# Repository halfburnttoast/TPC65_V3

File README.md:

# TPC65_V3
65C816 computer madness

This build replaces the TPC65-V2's CPU with a 65C816. It offers massive improvements, but requires additional circuitry to use bank switching.
On first boot, the CPU defaults to emulation mode. In emulation mode, the computer should be completely backwards compatible with V2 of this computer and all sofware. 

When emulation mode is turned off (see 65C816 datasheet for opcode sequence), the computer switches to 16-bit mode with a 24-bit (banked) address bus. 

Unfortunately, because of emulation mode, EEPROM must be located at the top-end of page 1 (0x000000 - 0x00FFFF). Because it follows the same memory map as V2, the memory map looks like this:

0x000000-0x007FFF - Base SRAM

0x008000-0x00BFFF - Memory-mapped IO

0x00C000-0x00FFFF - Base EEPROM + system vectors

Anything at or above 0x010000 is extended memory and requires banking through the 74x573 and 74x245. https://www.westerndesigncenter.com/wdc/documentation/w65c816s.pdf (page-44). 

The extended memory is currently mapped to the remaining address pins of the SRAM, which should give about 450K of extended RAM. Expanding EEPROM is not a priority as this computer has a built-in SD card module slot and is inteded to use the SD card for larger program loading.

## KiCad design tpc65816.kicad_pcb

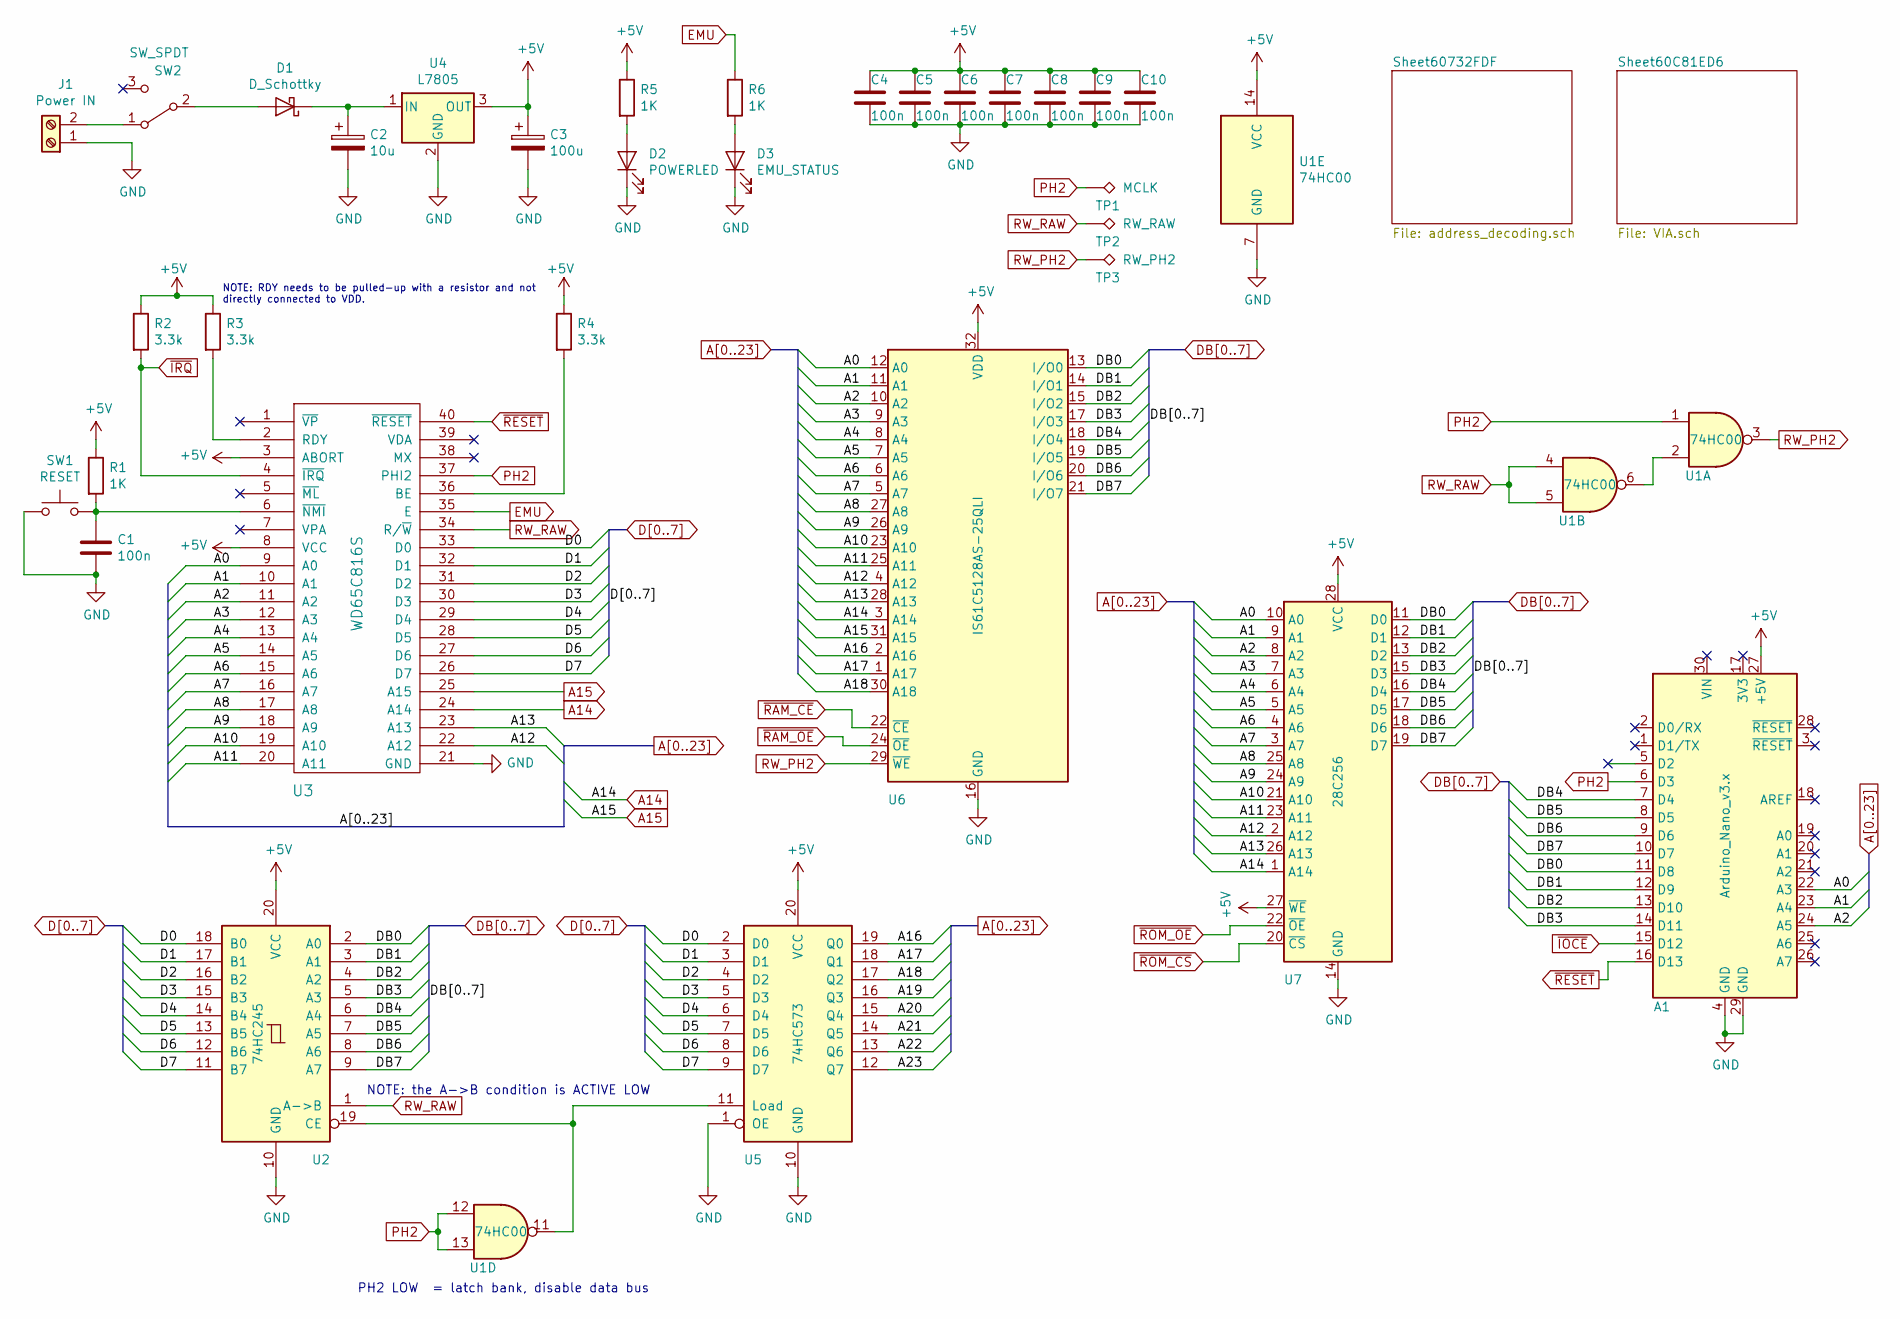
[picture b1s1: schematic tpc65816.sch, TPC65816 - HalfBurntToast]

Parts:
A1: Arduino_Nano_v3.x; Arduino_Nano
C1, C4, C5, C6, C7, C8, C9, C10: 100n; C_1206_3216Metric_Pad1.42x1.75mm_HandSolder
C2: 10u; CP_Radial_D4.0mm_P2.00mm
C3: 100u; CP_Radial_D4.0mm_P2.00mm
D1: D_Schottky; D_1206_3216Metric_Pad1.42x1.75mm_HandSolder
D2: POWERLED; LED_D5.0mm
D3: EMU_STATUS; LED_1206_3216Metric_Pad1.42x1.75mm_HandSolder
J1: Power IN; TerminalBlock_bornier-2_P5.08mm
R1, R5, R6: 1K; R_1206_3216Metric_Pad1.42x1.75mm_HandSolder
R2: 3.3k; R_Axial_DIN0207_L6.3mm_D2.5mm_P7.62mm_Horizontal
R3, R4: 3.3k; R_1206_3216Metric_Pad1.42x1.75mm_HandSolder
SW1: RESET; SW_PUSH_6mm
SW2: SW_SPDT; spdt_slide_switch
TP1: MCLK; TestPoint_Pad_1.0x1.0mm
TP2: RW_RAW; TestPoint_Pad_1.0x1.0mm
TP3: RW_PH2; TestPoint_Pad_1.0x1.0mm
U1: 74HC00; SOIC-14_3.9x8.7mm_P1.27mm
U2: 74HC245; SOIC-20W_7.5x12.8mm_P1.27mm
U3: WD65C816S; DIP-40_W15.24mm_Socket
U4: L7805; TO-220F-3_Horizontal_TabDown
U5: 74HC573; SOIC-20W_7.5x12.8mm_P1.27mm
U6: IS61C5128AS-25QLI; SSOP-32_11.305x20.495mm_P1.27mm
U7: 28C256; DIP-28_W15.24mm_Socket

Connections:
+5V: A1.27 (+5V), C3.1, C4.1, C5.1, C6.1, C7.1, C8.1, C9.1, C10.1, R1.1, R2.1, R3.1, R4.1, R5.1, U1.14 (VCC), U2.20 (VCC), U3.3 (ABORT), U3.8 (VCC), U4.3 (OUT), U5.20 (VCC), U6.32 (VDD), U7.27 (~WE), U7.28 (VCC); also elsewhere on the board
A0: A1.22 (A3), U3.9 (A0), U6.12 (A0), U7.10 (A0)
A1: A1.23 (A4), U3.10 (A1), U6.11 (A1), U7.9 (A1)
A2: A1.24 (A5), U3.11 (A2), U6.10 (A2), U7.8 (A2)
A3: U3.12 (A3), U6.9 (A3), U7.7 (A3); also elsewhere on the board
A4: U3.13 (A4), U6.8 (A4), U7.6 (A4); also elsewhere on the board
A5: U3.14 (A5), U6.7 (A5), U7.5 (A5); also elsewhere on the board
A6: U3.15 (A6), U6.6 (A6), U7.4 (A6); also elsewhere on the board
A7: U3.16 (A7), U6.5 (A7), U7.3 (A7); also elsewhere on the board
A8: U3.17 (A8), U6.27 (A8), U7.25 (A8); also elsewhere on the board
A9: U3.18 (A9), U6.26 (A9), U7.24 (A9)
A10: U3.19 (A10), U6.23 (A10), U7.21 (A10)
A11: U3.20 (A11), U6.25 (A11), U7.23 (A11)
A12: U3.22 (A12), U6.4 (A12), U7.2 (A12)
A13: U3.23 (A13), U6.28 (A13), U7.26 (A13)
A14: U3.24 (A14), U6.3 (A14), U7.1 (A14); also elsewhere on the board
A15: U3.25 (A15), U6.31 (A15); also elsewhere on the board
A16: U5.19 (Q0), U6.2 (A16); also elsewhere on the board
A17: U5.18 (Q1), U6.1 (A17); also elsewhere on the board
A18: U5.17 (Q2), U6.30 (A18); also elsewhere on the board
A19: U5.16 (Q3); also elsewhere on the board
A20: U5.15 (Q4); also elsewhere on the board
A21: U5.14 (Q5); also elsewhere on the board
A22: U5.13 (Q6); also elsewhere on the board
A23: U5.12 (Q7); also elsewhere on the board
D0: U2.18 (B0), U3.33 (D0), U5.2 (D0)
D1: U2.17 (B1), U3.32 (D1), U5.3 (D1)
D2: U2.16 (B2), U3.31 (D2), U5.4 (D2)
D3: U2.15 (B3), U3.30 (D3), U5.5 (D3)
D4: U2.14 (B4), U3.29 (D4), U5.6 (D4)
D5: U2.13 (B5), U3.28 (D5), U5.7 (D5)
D6: U2.12 (B6), U3.27 (D6), U5.8 (D6)
D7: U2.11 (B7), U3.26 (D7), U5.9 (D7)
DB0: A1.11 (D8), U2.2 (A0), U6.13 (I/O0), U7.11 (D0); also elsewhere on the board
DB1: A1.12 (D9), U2.3 (A1), U6.14 (I/O1), U7.12 (D1); also elsewhere on the board
DB2: A1.13 (D10), U2.4 (A2), U6.15 (I/O2), U7.13 (D2); also elsewhere on the board
DB3: A1.14 (D11), U2.5 (A3), U6.17 (I/O3), U7.15 (D3); also elsewhere on the board
DB4: A1.7 (D4), U2.6 (A4), U6.18 (I/O4), U7.16 (D4); also elsewhere on the board
DB5: A1.8 (D5), U2.7 (A5), U6.19 (I/O5), U7.17 (D5); also elsewhere on the board
DB6: A1.9 (D6), U2.8 (A6), U6.20 (I/O6), U7.18 (D6); also elsewhere on the board
DB7: A1.10 (D7), U2.9 (A7), U6.21 (I/O7), U7.19 (D7); also elsewhere on the board
EMU: R6.1, U3.35 (E)
GND: A1.4 (GND), A1.29 (GND), C1.2, C2.2, C3.2, C4.2, C5.2, C6.2, C7.2, C8.2, C9.2, C10.2, D2.1 (K), D3.1 (K), J1.1, SW1.1, U1.7 (GND), U2.10 (GND), U3.21 (GND), U4.2 (GND), U5.1 (OE), U5.10 (GND), U6.16 (GND), U7.14 (GND); also elsewhere on the board
unnamed: C1.1, R1.2, SW1.2, U3.6 (~NMI)
unnamed: C2.1, D1.1 (K), U4.1 (IN)
unnamed: D1.2 (A), SW2.2 (B)
unnamed: D2.2 (A), R5.2
unnamed: D3.2 (A), R6.2
unnamed: J1.2, SW2.1 (A)
unnamed: R3.2, U3.2 (RDY)
unnamed: R4.2, U3.36 (BE)
unnamed: U1.2, U1.6
unnamed: U1.11, U2.19 (CE), U5.11 (Load)
PH2: A1.6 (D3), TP1.1, U1.1, U1.12, U1.13, U3.37 (PHI2); also elsewhere on the board
RW_PH2: TP3.1, U1.3, U6.29 (~WE)
RW_RAW: TP2.1, U1.4, U1.5, U2.1 (A->B), U3.34 (R/~W); also elsewhere on the board
~IOCE: A1.15 (D12); also elsewhere on the board
~IRQ: R2.2, U3.4 (~IRQ); also elsewhere on the board
~RAM_CE: U6.22 (~CE), U6.24 (~OE); also elsewhere on the board
~RESET: A1.16 (D13), U3.40 (~RESET); also elsewhere on the board
~ROM_CS: U7.20 (~CS), U7.22 (~OE); also elsewhere on the board

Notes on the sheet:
NOTE: RDY needs to be pulled-up with a resistor and not directly connected to VDD.
NOTE: the A->B condition is ACTIVE LOW
PH2 LOW = latch bank, disable data bus

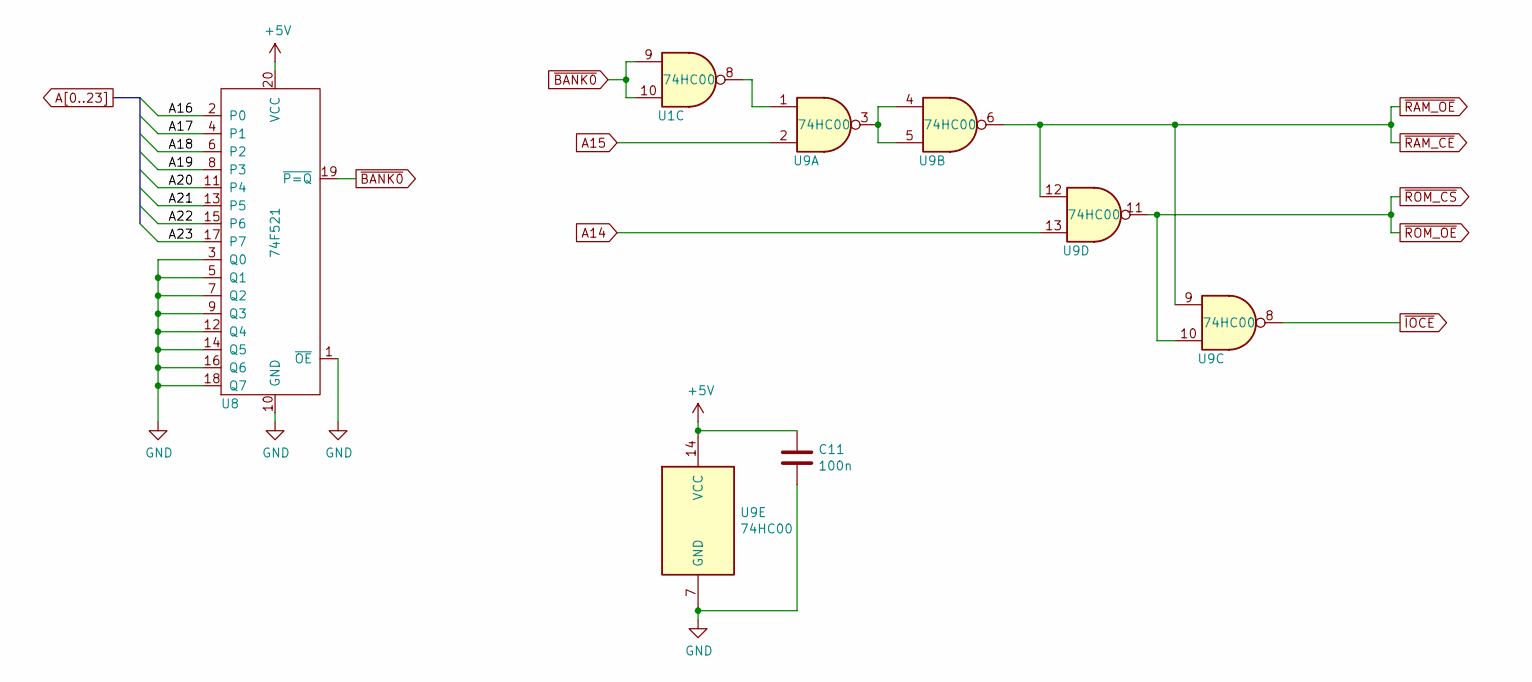
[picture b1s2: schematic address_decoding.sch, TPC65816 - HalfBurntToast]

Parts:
C11: 100n; C_1206_3216Metric_Pad1.42x1.75mm_HandSolder
U1, U9: 74HC00; SOIC-14_3.9x8.7mm_P1.27mm
U8: 74F521; SOIC-20W_7.5x12.8mm_P1.27mm

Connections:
+5V: C11.1, U8.20 (VCC), U9.14 (VCC); also elsewhere on the board
A14: U9.13; also elsewhere on the board
A15: U9.2; also elsewhere on the board
A16: U8.2 (P0); also elsewhere on the board
A17: U8.4 (P1); also elsewhere on the board
A18: U8.6 (P2); also elsewhere on the board
A19: U8.8 (P3); also elsewhere on the board
A20: U8.11 (P4); also elsewhere on the board
A21: U8.13 (P5); also elsewhere on the board
A22: U8.15 (P6); also elsewhere on the board
A23: U8.17 (P7); also elsewhere on the board
GND: C11.2, U8.1 (~OE), U8.3 (Q0), U8.5 (Q1), U8.7 (Q2), U8.9 (Q3), U8.10 (GND), U8.12 (Q4), U8.14 (Q5), U8.16 (Q6), U8.18 (Q7), U9.7 (GND); also elsewhere on the board
unnamed: U1.8, U9.1
unnamed: U9.3, U9.4, U9.5
~BANK0: U1.9, U1.10, U8.19 (~P=Q)
~IOCE: U9.8; also elsewhere on the board
~RAM_CE: U9.6, U9.9, U9.12; also elsewhere on the board
~ROM_CS: U9.10, U9.11; also elsewhere on the board

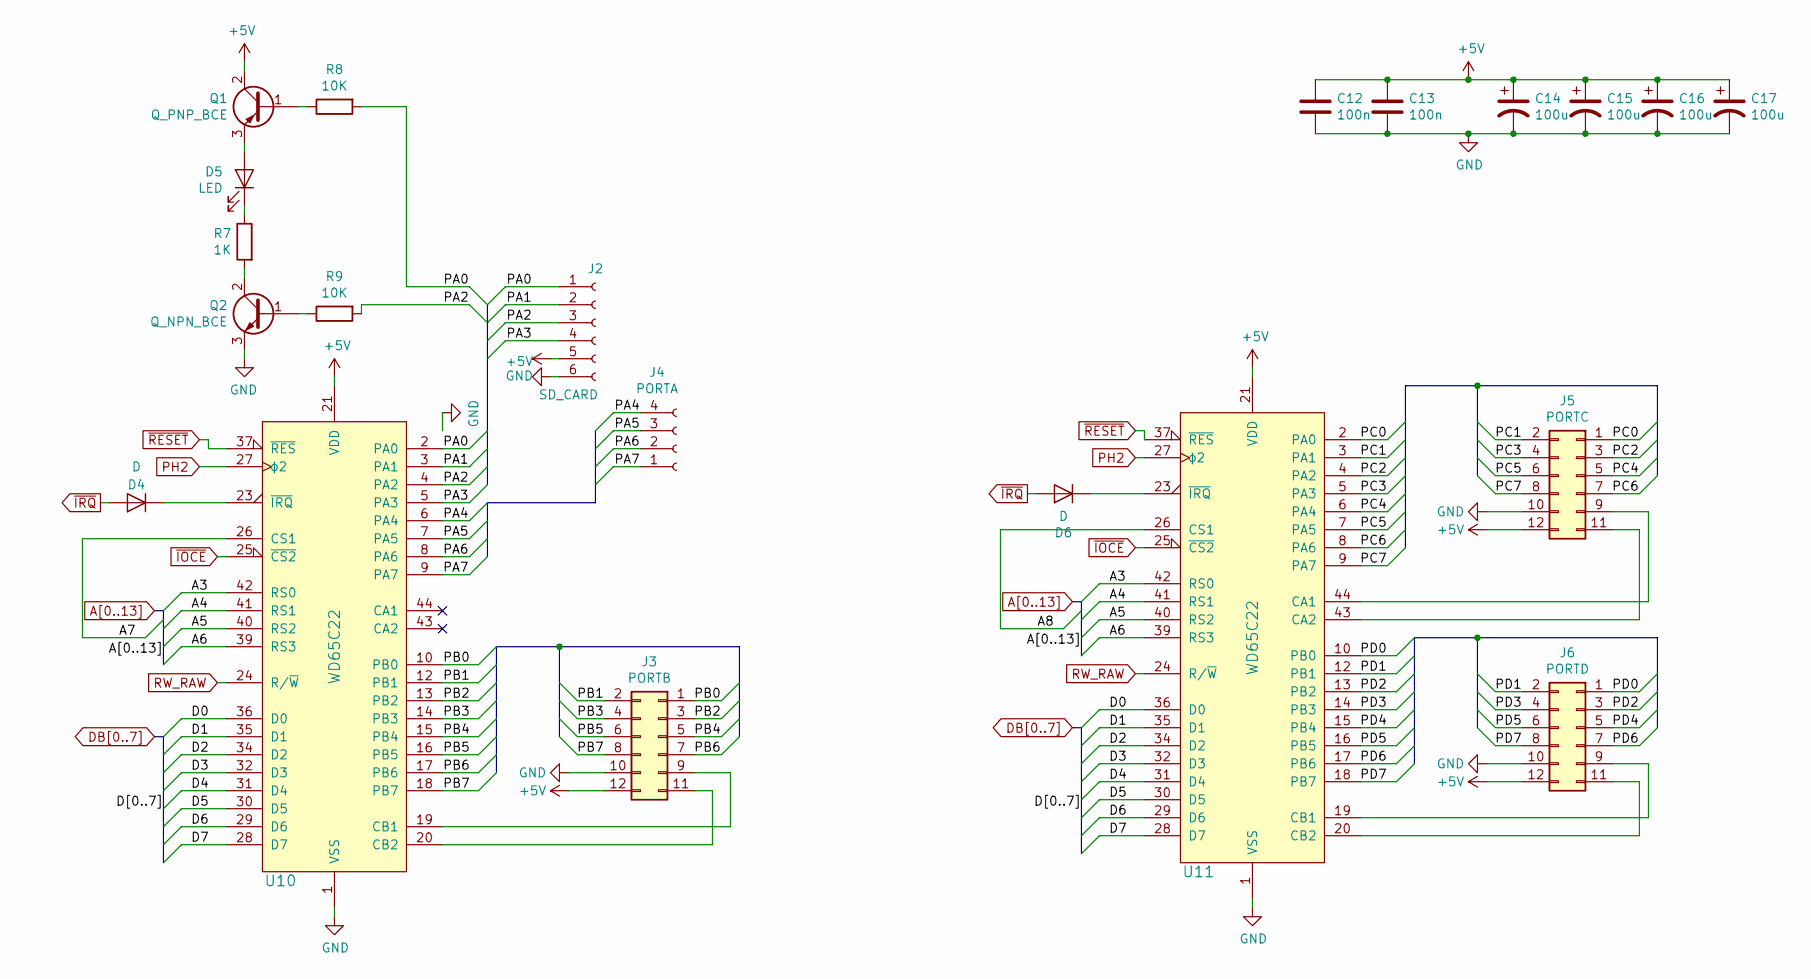
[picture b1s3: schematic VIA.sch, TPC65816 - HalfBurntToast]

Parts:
C12, C13: 100n; C_1206_3216Metric_Pad1.42x1.75mm_HandSolder
C14, C15, C16, C17: 100u; CP_Radial_D4.0mm_P2.00mm
D4, D6: D; D_T-1_P5.08mm_Horizontal
D5: LED; LED_1206_3216Metric_Pad1.42x1.75mm_HandSolder
J2: SD_CARD; PinSocket_1x06_P2.54mm_Vertical
J3: PORTB; PinSocket_2x06_P2.54mm_Vertical
J4: PORTA; PinSocket_2x02_P2.54mm_Vertical
J5: PORTC; PinSocket_2x06_P2.54mm_Vertical
J6: PORTD; PinSocket_2x06_P2.54mm_Vertical
Q1: Q_PNP_BCE; SOT-23_Handsoldering
Q2: Q_NPN_BCE; SOT-23_Handsoldering
R7: 1K; R_1206_3216Metric_Pad1.42x1.75mm_HandSolder
R8, R9: 10K; R_1206_3216Metric_Pad1.42x1.75mm_HandSolder
U10, U11: WD65C22; PLCC-44_THT-Socket

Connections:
+5V: C12.1, C13.1, C14.1, C15.1, C16.1, C17.1, J2.5, J3.12, J5.12, J6.12, Q1.2 (C), U10.21 (VDD), U11.21 (VDD); also elsewhere on the board
/Sheet60C81ED6/PA0: J2.1, R8.2, U10.2 (PA0)
/Sheet60C81ED6/PA1: J2.2, U10.3 (PA1)
/Sheet60C81ED6/PA2: J2.3, R9.2, U10.4 (PA2)
/Sheet60C81ED6/PA3: J2.4, U10.5 (PA3)
/Sheet60C81ED6/PA4: J4.4, U10.6 (PA4)
/Sheet60C81ED6/PA5: J4.3, U10.7 (PA5)
/Sheet60C81ED6/PA6: J4.2, U10.8 (PA6)
/Sheet60C81ED6/PA7: J4.1, U10.9 (PA7)
/Sheet60C81ED6/PB0: J3.1, U10.10 (PB0)
/Sheet60C81ED6/PB1: J3.2, U10.12 (PB1)
/Sheet60C81ED6/PB2: J3.3, U10.13 (PB2)
/Sheet60C81ED6/PB3: J3.4, U10.14 (PB3)
/Sheet60C81ED6/PB4: J3.5, U10.15 (PB4)
/Sheet60C81ED6/PB5: J3.6, U10.16 (PB5)
/Sheet60C81ED6/PB6: J3.7, U10.17 (PB6)
/Sheet60C81ED6/PB7: J3.8, U10.18 (PB7)
/Sheet60C81ED6/PC0: J5.1, U11.2 (PA0)
/Sheet60C81ED6/PC1: J5.2, U11.3 (PA1)
/Sheet60C81ED6/PC2: J5.3, U11.4 (PA2)
/Sheet60C81ED6/PC3: J5.4, U11.5 (PA3)
/Sheet60C81ED6/PC4: J5.5, U11.6 (PA4)
/Sheet60C81ED6/PC5: J5.6, U11.7 (PA5)
/Sheet60C81ED6/PC6: J5.7, U11.8 (PA6)
/Sheet60C81ED6/PC7: J5.8, U11.9 (PA7)
/Sheet60C81ED6/PD0: J6.1, U11.10 (PB0)
/Sheet60C81ED6/PD1: J6.2, U11.12 (PB1)
/Sheet60C81ED6/PD2: J6.3, U11.13 (PB2)
/Sheet60C81ED6/PD3: J6.4, U11.14 (PB3)
/Sheet60C81ED6/PD4: J6.5, U11.15 (PB4)
/Sheet60C81ED6/PD5: J6.6, U11.16 (PB5)
/Sheet60C81ED6/PD6: J6.7, U11.17 (PB6)
/Sheet60C81ED6/PD7: J6.8, U11.18 (PB7)
A3: U10.42 (RS0), U11.42 (RS0); also elsewhere on the board
A4: U10.41 (RS1), U11.41 (RS1); also elsewhere on the board
A5: U10.40 (RS2), U11.40 (RS2); also elsewhere on the board
A6: U10.39 (RS3), U11.39 (RS3); also elsewhere on the board
A7: U10.26 (CS1); also elsewhere on the board
A8: U11.26 (CS1); also elsewhere on the board
DB0: U10.36 (D0), U11.36 (D0); also elsewhere on the board
DB1: U10.35 (D1), U11.35 (D1); also elsewhere on the board
DB2: U10.34 (D2), U11.34 (D2); also elsewhere on the board
DB3: U10.32 (D3), U11.32 (D3); also elsewhere on the board
DB4: U10.31 (D4), U11.31 (D4); also elsewhere on the board
DB5: U10.30 (D5), U11.30 (D5); also elsewhere on the board
DB6: U10.29 (D6), U11.29 (D6); also elsewhere on the board
DB7: U10.28 (D7), U11.28 (D7); also elsewhere on the board
GND: C12.2, C13.2, C14.2, C15.2, C16.2, C17.2, J2.6, J3.10, J5.10, J6.10, Q2.3 (E), U10.1 (VSS), U11.1 (VSS); also elsewhere on the board
unnamed: D4.1 (K), U10.23 (~IRQ)
unnamed: D5.1 (K), R7.1
unnamed: D5.2 (A), Q1.3 (E)
unnamed: D6.1 (K), U11.23 (~IRQ)
unnamed: J3.9, U10.19 (CB1)
unnamed: J3.11, U10.20 (CB2)
unnamed: J5.9, U11.44 (CA1)
unnamed: J5.11, U11.43 (CA2)
unnamed: J6.9, U11.19 (CB1)
unnamed: J6.11, U11.20 (CB2)
unnamed: Q1.1 (B), R8.1
unnamed: Q2.1 (B), R9.1
unnamed: Q2.2 (C), R7.2
PH2: U10.27 (ϕ2), U11.27 (ϕ2); also elsewhere on the board
RW_RAW: U10.24 (R/~W), U11.24 (R/~W); also elsewhere on the board
~IOCE: U10.25 (~CS2), U11.25 (~CS2); also elsewhere on the board
~IRQ: D4.2 (A), D6.2 (A); also elsewhere on the board
~RESET: U10.37 (~RES), U11.37 (~RES); also elsewhere on the board

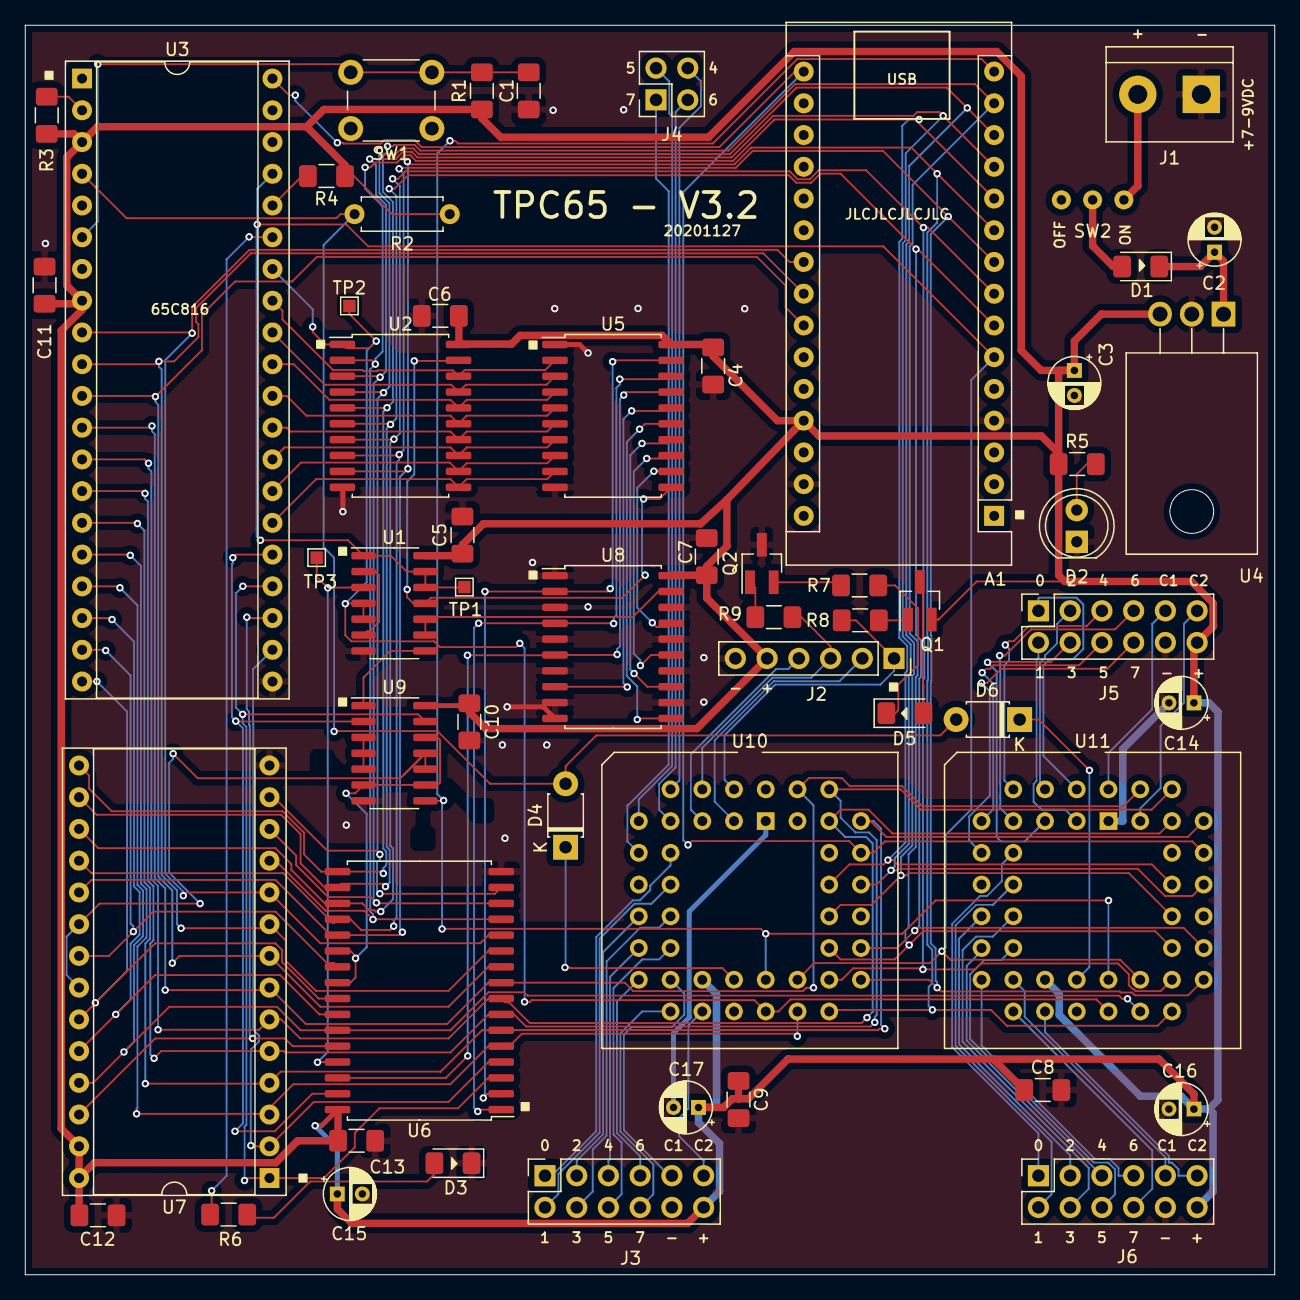
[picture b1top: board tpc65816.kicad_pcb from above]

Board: 2 copper layers, 100.0 x 100.0 mm, 57 parts (0 on the bottom side), 109 nets.

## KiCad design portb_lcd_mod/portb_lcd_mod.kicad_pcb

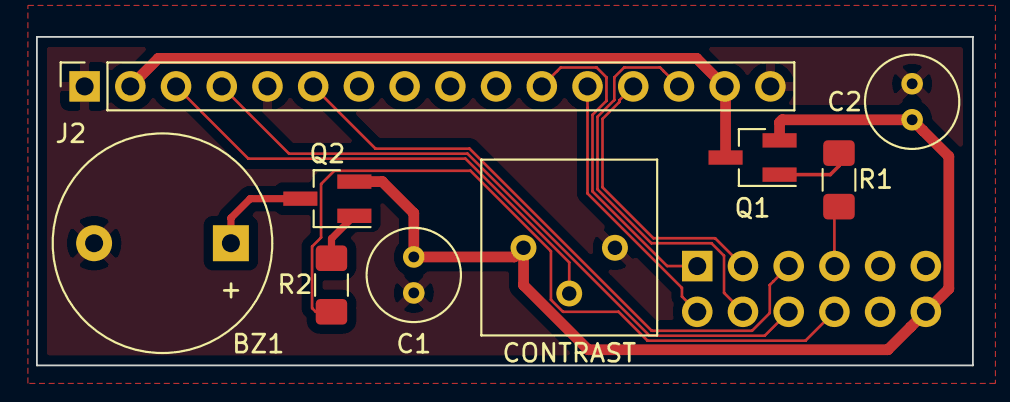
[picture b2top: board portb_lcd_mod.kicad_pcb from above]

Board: 2 copper layers, 52.0 x 18.2 mm, 10 parts (1 on the bottom side), 15 nets.

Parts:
BZ1: Active Buzzer; Buzzer_12x9.5RM7.6
C1: 47u; C_Radial_D5.0mm_H7.0mm_P2.00mm
C2: 220u; C_Radial_D5.0mm_H7.0mm_P2.00mm
CONTRAST: R_POT; Potentiometer_Bourns_3386P_Vertical
J1: Conn_02x06_Odd_Even; PinHeader_2x06_P2.54mm_Vertical
J2: Conn_01x16_Female; PinSocket_1x16_P2.54mm_Vertical
Q1, Q2: Q_PNP_BJT; SOT-23_Handsoldering
R1, R2: R; R_1206_3216Metric_Pad1.42x1.75mm_HandSolder

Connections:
+5V: C1.1, C2.1, CONTRAST.1, J1.12, Q1.2, Q2.2
/A: J2.2, J2.15, Q1.3
/D4: J1.1, J2.11
/D5: J1.2, J2.12
/D6: J1.3, J2.13
/D7: J1.4, J2.14
/V0: CONTRAST.2, J2.3
E: J1.5, J2.6
GND: BZ1.2, C1.2, C2.2, CONTRAST.3, J1.10, J2.1, J2.5, J2.16
unnamed: BZ1.1, Q2.3
unnamed: J1.7, R1.2
unnamed: J1.8, R2.2
unnamed: Q1.1, R1.1
unnamed: Q2.1, R2.1
RS: J1.6, J2.4

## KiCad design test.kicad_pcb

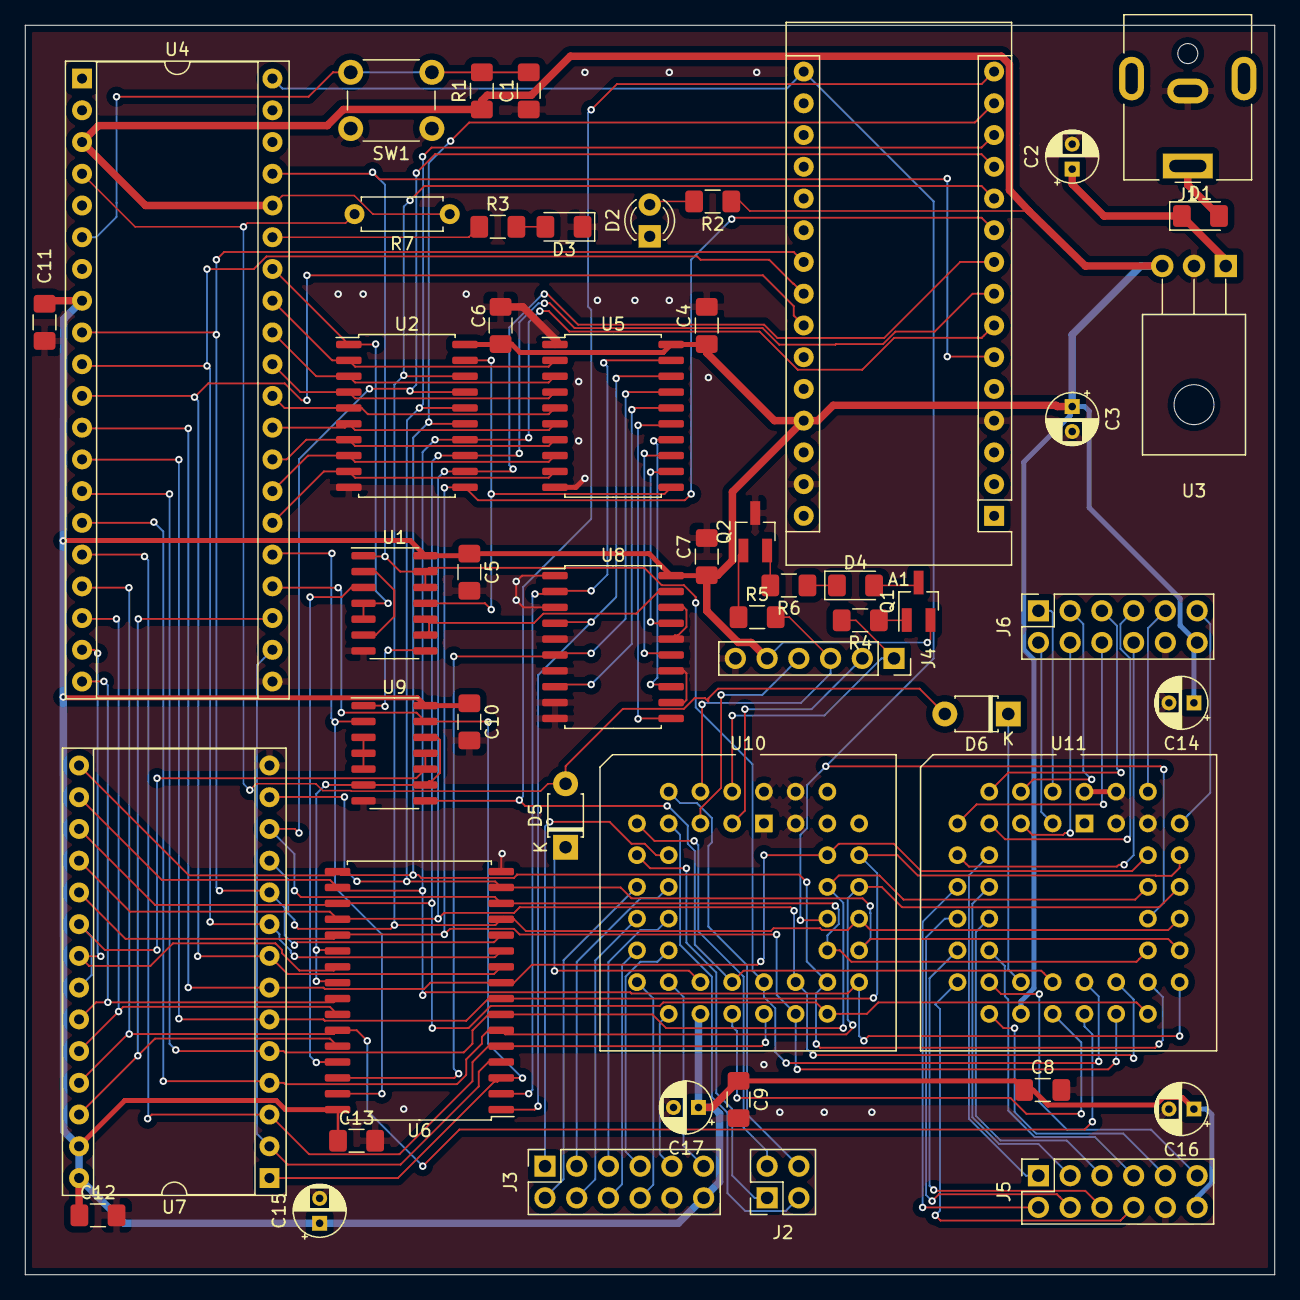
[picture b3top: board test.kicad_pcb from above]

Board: 2 copper layers, 100.0 x 100.0 mm, 51 parts (0 on the bottom side), 107 nets.

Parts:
A1: Arduino_Nano_v3.x; Arduino_Nano
C1, C4, C5, C6, C7, C8, C9, C10, C11, C12, C13: 100n; C_1206_3216Metric_Pad1.42x1.75mm_HandSolder
C2: 10u; CP_Radial_D4.0mm_P2.00mm
C3, C14, C15, C16, C17: 100u; CP_Radial_D4.0mm_P2.00mm
D1: D_Schottky; D_1206_3216Metric_Pad1.42x1.75mm_HandSolder
D2: POWERLED; LED_D3.0mm
D3: EMU_STATUS; LED_1206_3216Metric_Pad1.42x1.75mm_HandSolder
D4: LED; LED_1206_3216Metric_Pad1.42x1.75mm_HandSolder
D5, D6: D; D_T-1_P5.08mm_Horizontal
J1: Barrel_Jack; BarrelJack_CUI_PJ-063AH_Horizontal
J2: PORTA; PinSocket_2x02_P2.54mm_Vertical
J3: PORTB; PinSocket_2x06_P2.54mm_Vertical
J4: SD_CARD; PinSocket_1x06_P2.54mm_Vertical
J5: PORTD; PinSocket_2x06_P2.54mm_Vertical
J6: PORTC; PinSocket_2x06_P2.54mm_Vertical
Q1: Q_PNP_BCE; SOT-23_Handsoldering
Q2: Q_NPN_BCE; SOT-23_Handsoldering
R1, R2, R3, R6: 1K; R_1206_3216Metric_Pad1.42x1.75mm_HandSolder
R4, R5: 10K; R_1206_3216Metric_Pad1.42x1.75mm_HandSolder
R7: 3.3k; R_Axial_DIN0207_L6.3mm_D2.5mm_P7.62mm_Horizontal
SW1: RESET; SW_PUSH_6mm
U1, U9: 74HC00; SOIC-14_3.9x8.7mm_P1.27mm
U2: 74LS245; SOIC-20W_7.5x12.8mm_P1.27mm
U3: L7805; TO-126-3_Horizontal_TabDown
U4: WD65C816S; DIP-40_W15.24mm_Socket
U5: 74LS573; SOIC-20W_7.5x12.8mm_P1.27mm
U6: IS61C5128AS-25QLI; SSOP-32_11.305x20.495mm_P1.27mm
U7: 28C256; DIP-28_W15.24mm_Socket
U8: 74F521; SOIC-20W_7.5x12.8mm_P1.27mm
U10, U11: WD65C22; PLCC-44_THT-Socket

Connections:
+5V: A1.27, C3.1, C4.1, C5.1, C6.1, C7.1, C8.1, C9.1, C10.1, C11.1, C12.1, C13.1, C14.1, C15.1, C16.1, C17.1, J3.12, J4.5, J5.12, J6.12, Q1.2, R1.1, R2.1, R7.1, U1.14, U2.20, U3.3, U4.3, U4.8, U4.36, U5.20, U6.32, U7.27, U7.28, U8.20, U9.14, U10.20, U11.20
/Sheet60C81ED6/PA0: J4.1, R4.2, U10.2
/Sheet60C81ED6/PA1: J4.2, U10.3
/Sheet60C81ED6/PA2: J4.3, R5.2, U10.4
/Sheet60C81ED6/PA3: J4.4, U10.5
/Sheet60C81ED6/PA4: J2.4, U10.6
/Sheet60C81ED6/PA5: J2.3, U10.7
/Sheet60C81ED6/PA6: J2.2, U10.8
/Sheet60C81ED6/PA7: J2.1, U10.9
/Sheet60C81ED6/PB0: J3.1, U10.10
/Sheet60C81ED6/PB1: J3.2, U10.11
/Sheet60C81ED6/PB2: J3.3, U10.12
/Sheet60C81ED6/PB3: J3.4, U10.13
/Sheet60C81ED6/PB4: J3.5, U10.14
/Sheet60C81ED6/PB5: J3.6, U10.15
/Sheet60C81ED6/PB6: J3.7, U10.16
/Sheet60C81ED6/PB7: J3.8, U10.17
/Sheet60C81ED6/PC0: J6.1, U11.2
/Sheet60C81ED6/PC1: J6.2, U11.3
/Sheet60C81ED6/PC2: J6.3, U11.4
/Sheet60C81ED6/PC3: J6.4, U11.5
/Sheet60C81ED6/PC4: J6.5, U11.6
/Sheet60C81ED6/PC5: J6.6, U11.7
/Sheet60C81ED6/PC6: J6.7, U11.8
/Sheet60C81ED6/PC7: J6.8, U11.9
/Sheet60C81ED6/PD0: J5.1, U11.10
/Sheet60C81ED6/PD1: J5.2, U11.11
/Sheet60C81ED6/PD2: J5.3, U11.12
/Sheet60C81ED6/PD3: J5.4, U11.13
/Sheet60C81ED6/PD4: J5.5, U11.14
/Sheet60C81ED6/PD5: J5.6, U11.15
/Sheet60C81ED6/PD6: J5.7, U11.16
/Sheet60C81ED6/PD7: J5.8, U11.17
A0: A1.22, U4.9, U6.12, U7.10
A1: A1.23, U4.10, U6.11, U7.9
A2: A1.24, U4.11, U6.10, U7.8
A3: U4.12, U6.9, U7.7, U10.38, U11.38
A4: U4.13, U6.8, U7.6, U10.37, U11.37
A5: U4.14, U6.7, U7.5, U10.36, U11.36
A6: U4.15, U6.6, U7.4, U10.35, U11.35
A7: U4.16, U6.5, U7.3, U10.24
A8: U4.17, U6.27, U7.25, U11.24
A9: U4.18, U6.26, U7.24
A10: U4.19, U6.23, U7.21
A11: U4.20, U6.25, U7.23
A12: U4.22, U6.4, U7.2
A13: U4.23, U6.28, U7.26
A14: U4.24, U6.3, U7.1, U9.13
A15: U4.25, U6.31, U9.2
A16: U5.19, U6.2, U8.2
A17: U5.18, U6.1, U8.4
A18: U5.17, U6.30, U8.6
A19: U5.16, U8.8
A20: U5.15, U8.11
A21: U5.14, U8.13
A22: U5.13, U8.15
A23: U5.12, U8.17
D0: U2.2, U4.33, U5.2
D1: U2.3, U4.32, U5.3
D2: U2.4, U4.31, U5.4
D3: U2.5, U4.30, U5.5
D4: U2.6, U4.29, U5.6
D5: U2.7, U4.28, U5.7
D6: U2.8, U4.27, U5.8
D7: U2.9, U4.26, U5.9
DB0: A1.11, U2.18, U6.13, U7.11, U10.33, U11.33
DB1: A1.12, U2.17, U6.14, U7.12, U10.32, U11.32
DB2: A1.13, U2.16, U6.15, U7.13, U10.31, U11.31
DB3: A1.14, U2.15, U6.17, U7.15, U10.30, U11.30
DB4: A1.7, U2.14, U6.18, U7.16, U10.29, U11.29
DB5: A1.8, U2.13, U6.19, U7.17, U10.28, U11.28
DB6: A1.9, U2.12, U6.20, U7.18, U10.27, U11.27
DB7: A1.10, U2.11, U6.21, U7.19, U10.26, U11.26
EMU: R3.1, U4.35
GND: A1.4, A1.29, C1.2, C2.2, C3.2, C4.2, C5.2, C6.2, C7.2, C8.2, C9.2, C10.2, C11.2, C12.2, C13.2, C14.2, C15.2, C16.2, C17.2, D2.1, D3.1, J1.2, J3.10, J4.6, J5.10, J6.10, Q2.3, SW1.1, U1.7, U2.10, U3.2, U4.21, U5.1, U5.10, U6.16, U7.14, U8.1, U8.3, U8.5, U8.7, U8.9, U8.10, U8.12, U8.14, U8.16, U8.18, U9.7, U10.1, U10.42, U10.43, U10.44, U11.1, U11.41, U11.42, U11.43, U11.44
unnamed: C1.1, R1.2, SW1.2, U4.6
unnamed: C2.1, D1.1, U3.1
unnamed: D1.2, J1.1
unnamed: D2.2, R2.2
unnamed: D3.2, R3.2
unnamed: D4.1, R6.1
unnamed: D4.2, Q1.3
unnamed: D5.1, U10.21
unnamed: D6.1, U11.21
unnamed: J3.9, U10.18
unnamed: J3.11, U10.19
unnamed: J5.9, U11.18
unnamed: J5.11, U11.19
unnamed: J6.9, U11.40
unnamed: J6.11, U11.39
unnamed: Q1.1, R4.1
unnamed: Q2.1, R5.1
unnamed: Q2.2, R6.2
unnamed: U1.2, U1.6
unnamed: U1.8, U9.1
unnamed: U1.11, U2.19, U5.11
unnamed: U9.3, U9.4, U9.5
PH2: A1.6, U1.1, U1.12, U1.13, U4.37, U10.25, U11.25
RW_RAW: U10.22, U11.22
RW_RAW_PH2: U1.3, U6.29
RW_RAW_RAW: U1.4, U1.5, U2.1, U4.34
~BANK0: U1.9, U1.10, U8.19
~IOCE: A1.15, U9.8, U10.23, U11.23
~IRQ: D5.2, D6.2, R7.2, U4.4
~RAM_CE: U6.22, U6.24, U9.6, U9.9, U9.12
~RESET: A1.16, U4.40, U10.34, U11.34
~ROM_CS: U7.20, U7.22, U9.10, U9.11

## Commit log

2020-11-18 Initial layout - NOT VERIFIED TO WORK
    Initial layout of PCB. There's a very high chance there are errors made either in the schematic and/or layout. The chip layout may also not be as tidy or efficient as it can be.
2020-11-18 Create LICENSE
2020-11-19 Edit to main schematic and layout
2020-11-20 Minor cleanup and repositioning - fabricated
    Schematic verified. Added power switch. Repositioned PORT A. Cleanup of some traces. Added silkscreen markings.
    Board has been sent to fabrication as of this commit.
2020-11-21 Fixed floating rdy pin
2020-11-22 Fill update
2020-11-22 Fix to RDY pin
    RDY needs to be pulled up with a resistor and not linked to VDD directly. Unlike the 65c02, RDY on the 65c816 is bidirectional and can, under some circumstances, attempt to pull itself down. If it's 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
2020-11-25 Track cleanup
2020-11-27 MAJOR FIXES - UNTESTED
    Fixes for voltage regulator and barrel jack footprint. Fix for 245 direction. Fix for 65C22 PLCC pin layout. Complete rerouting of board.
2020-12-04 Fix for bank decoder logic
